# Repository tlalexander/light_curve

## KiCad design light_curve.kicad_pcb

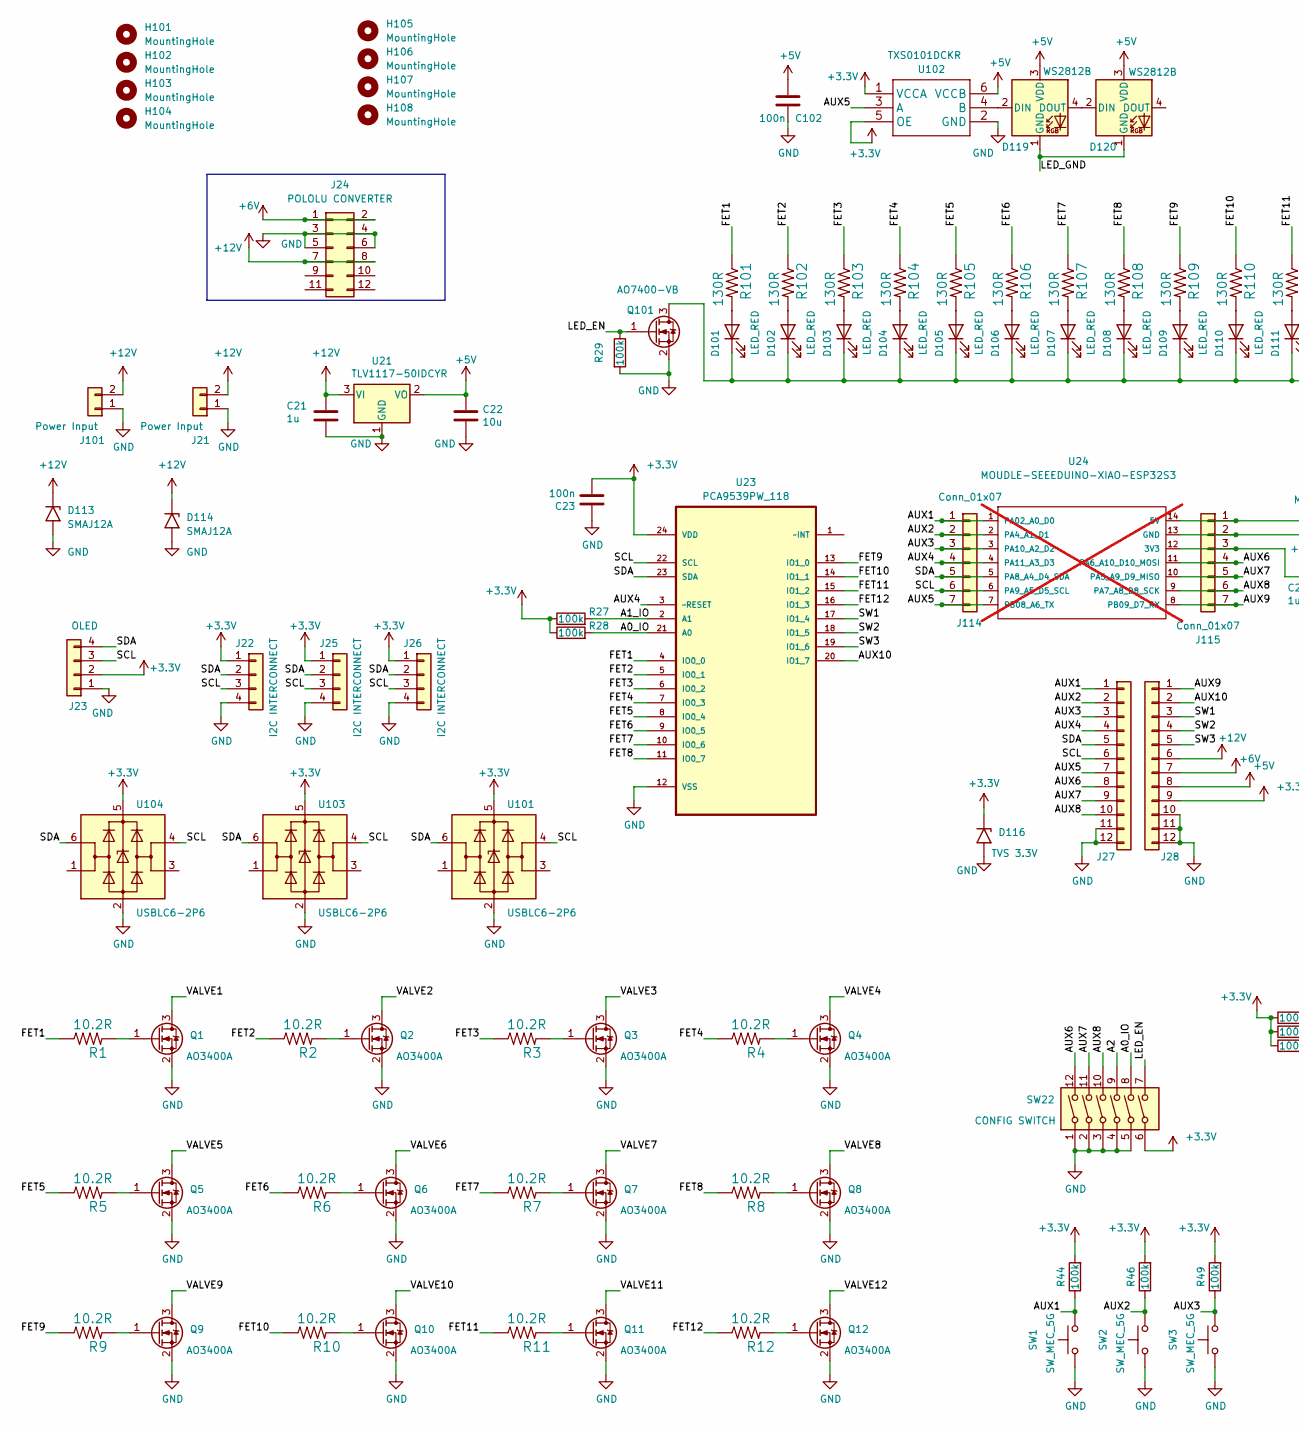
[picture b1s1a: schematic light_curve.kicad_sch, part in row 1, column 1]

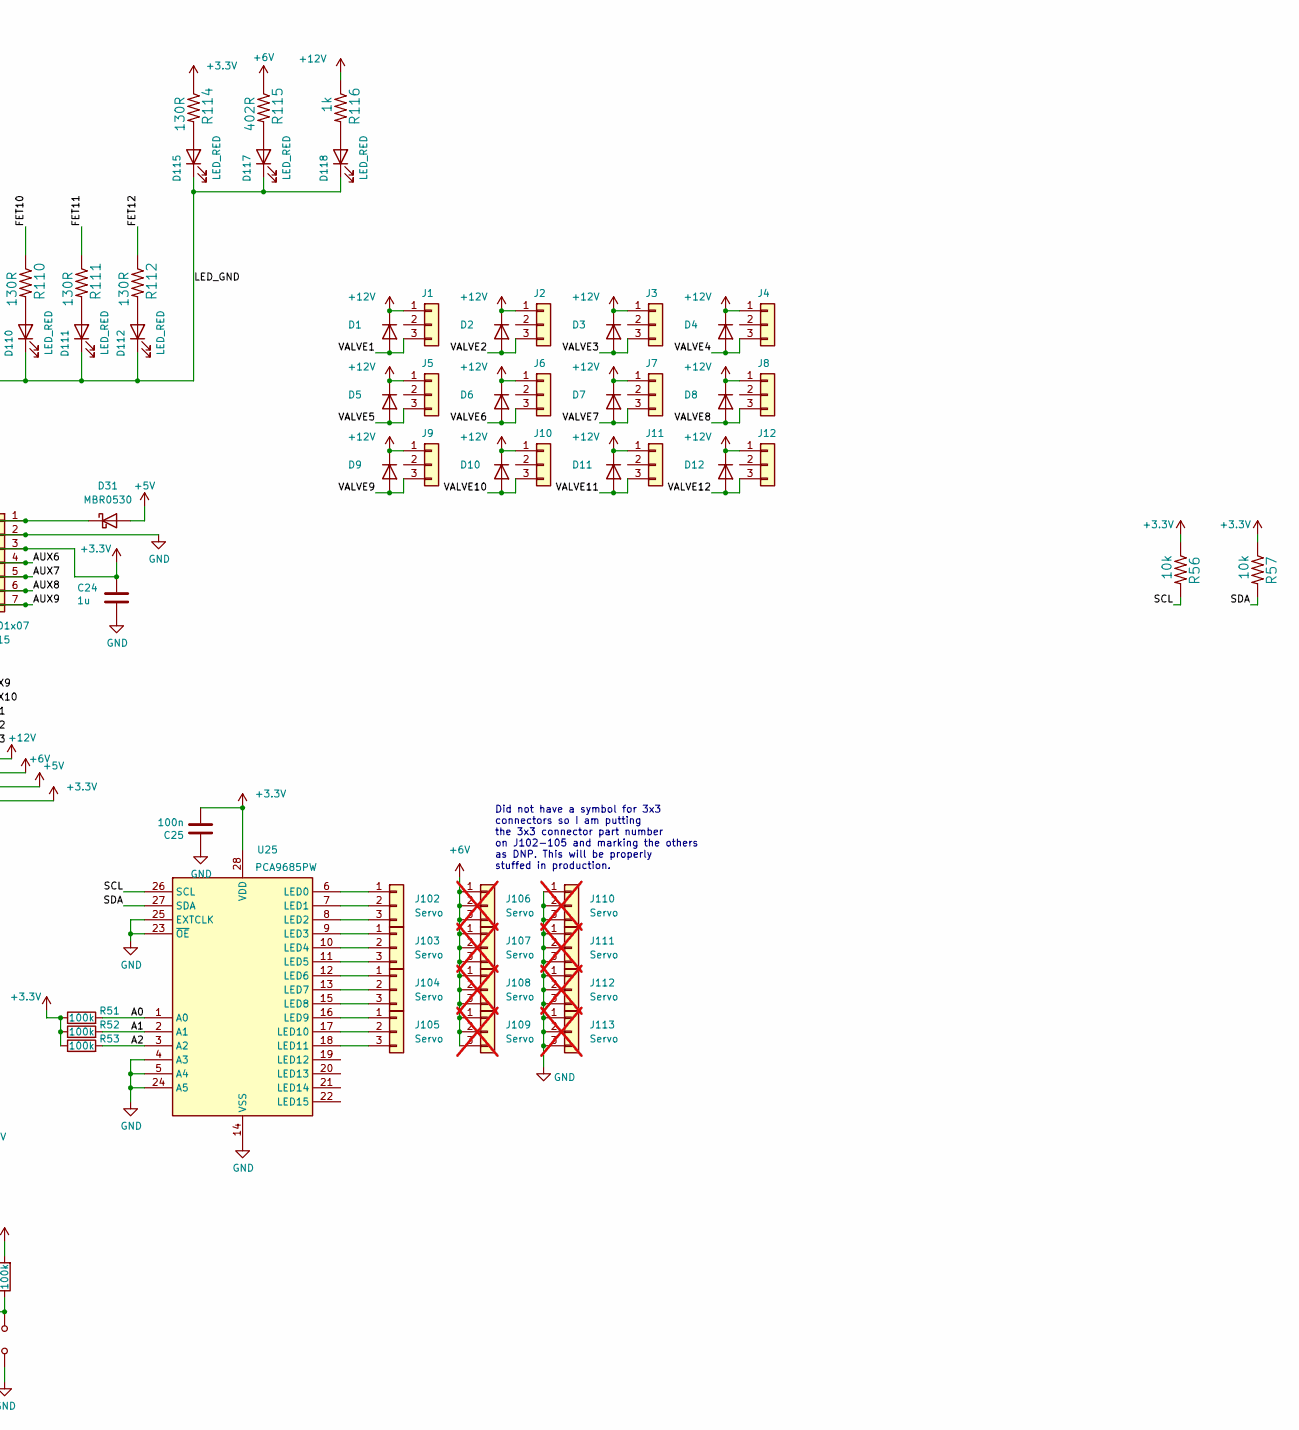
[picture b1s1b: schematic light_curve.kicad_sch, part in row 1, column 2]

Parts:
C21, C24: 1u; C_0603_1608Metric; LCSC C15849
C22: 10u; C_0805_2012Metric; LCSC C15850
C23, C25, C102: 100n; C_0603_1608Metric; LCSC C14663
D1, D2, D3, D4, D5, D6, D7, D8, D9, D10, D11, D12: D; D_SMA; LCSC C95872
D31: MBR0530; D_SOD-123; LCSC C77336
D101, D102, D103, D104, D105, D106, D107, D108, D109, D110, D111, D112, D115, D117, D118: LED_RED; LED_0603_1608Metric; MPN LTST-C150KRKT; Digikey 160-1405-1-ND
D113, D114: SMAJ12A; D_SMA; LCSC C89613
D116: TVS 3.3V; D_SOD-523; MPN ESD5Z3V3; LCSC C2841409
D119, D120: WS2812B; LED_WS2812_3528_3.5x2.8mm_P1.5mm; LCSC C2890364
H101, H102, H103, H104: MountingHole; MountingHole_4.5mm
H105, H106, H107, H108: MountingHole; MountingHole_2.5mm
J1, J2, J3, J4, J5, J6, J7, J8, J9, J10, J11, J12: Valve Conn; BOOMELE-2510-3A_1x03_P2.54mm_Vertical; LCSC C509148
J21, J101: Power Input; AMASS_XT30PW-F_1x02_P2.50mm_Horizontal; LCSC C2913282
J22, J25, J26: I2C INTERCONNECT; PINREX-744-81-04TW00 _1x04_P2.54mm_Vertical; LCSC C2982033
J23: OLED; PinHeader_1x04_P2.54mm_Vertical; LCSC C2718488
J24: POLOLU CONVERTER; PinHeader_2x06_P2.54mm_Vertical
J27, J28: A2541WV-12P; PinHeader_1x12_P2.54mm_Vertical; LCSC C1121851
J102, J103, J104, J105: Servo; PinHeader_1x03_P2.54mm_Vertical; LCSC C7429377
J106, J107, J108, J109, J110, J111, J112, J113: Servo; PinHeader_1x03_P2.54mm_Vertical; not fitted
J114, J115: Conn_01x07; PinSocket_1x07_P2.54mm_Vertical; LCSC C2897370
Q1, Q2, Q3, Q4, Q5, Q6, Q7, Q8, Q9, Q10, Q11, Q12: AO3400A; SOT-23; LCSC C347475
Q101: AO7400-VB; SOT-323_SC-70; LCSC C879165
R1, R2, R3, R4, R5, R6, R7, R8, R9, R10, R11, R12: 10.2R; R_0603_1608Metric; LCSC C2933129
R27, R28, R29, R44, R46, R49, R51, R52, R53: 100k; R_0603_1608Metric; LCSC C14675
R56, R57: 10k; R_0603_1608Metric; LCSC C25804
R101, R102, R103, R104, R105, R106, R107, R108, R109, R110, R111, R112, R114: 130R; R_0603_1608Metric; LCSC C22796
R115: 402R; R_0603_1608Metric; LCSC C2683044
R116: 1k; R_0603_1608Metric; LCSC C253329
SW1, SW2, SW3: SW_MEC_5G; SW_TS_1101_C_W; LCSC C318938
SW22: CONFIG SWITCH; SW_DIP_SPSTx06_Slide_KingTek_DSHP06TS_W7.62mm_P1.27mm; LCSC C40737
U21: TLV1117-50IDCYR; SOT-223-3_TabPin2; LCSC C15512
U23: PCA9539PW_118; TSSOP-24_4.4x7.8mm_P0.65mm; MPN PCA9539PW,118; LCSC C2687996
U24: MOUDLE-SEEEDUINO-XIAO-ESP32S3; MOUDLE14P-SMD-2.54-21X17.8MM; not fitted
U25: PCA9685PW; TSSOP-28_4.4x9.7mm_P0.65mm; LCSC C2678753
U101, U103, U104: USBLC6-2P6; SOT-666; LCSC C2827693
U102: TXS0101DCKR; SOT-363_SC-70-6; LCSC C132031

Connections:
+3.3V: C23.2, C24.1, C25.2, D116.1 (A1), J22.1, J23.2, J25.1, J26.1, J28.9, J115.3, R27.1, R28.1, R44.2, R46.2, R49.2, R51.1, R52.1, R53.1, R56.1, R57.1, R114.1, SW22.6, U23.24 (VDD), U24.12 (3V3), U25.28 (VDD), U101.5 (VBUS), U102.1 (VCCA), U102.5 (OE), U103.5 (VBUS), U104.5 (VBUS)
+5V: C22.1, C102.1, D31.2 (A), D119.3 (VDD), D120.3 (VDD), J28.8, U21.2 (VO), U102.6 (VCCB)
+6V: J24.1, J24.2, J28.7, J106.1, J106.2, J106.3, J107.1, J107.2, J107.3, J108.1, J108.2, J108.3, J109.1, J109.2, J109.3, R115.1
+12V: C21.1, D1.1 (K), D2.1 (K), D3.1 (K), D4.1 (K), D5.1 (K), D6.1 (K), D7.1 (K), D8.1 (K), D9.1 (K), D10.1 (K), D11.1 (K), D12.1 (K), D113.1 (A1), D114.1 (A1), J1.1, J2.1, J3.1, J4.1, J5.1, J6.1, J7.1, J8.1, J9.1, J10.1, J11.1, J12.1, J21.2, J24.7, J24.8, J28.6, J101.2, R116.1, U21.3 (VI)
/A0: R51.2, U25.1 (A0)
/A0_IO: R28.2, SW22.8, U23.21 (A0)
/A1: R52.2, U25.2 (A1)
/A1_IO: R27.2, U23.2 (A1)
/A2: R53.2, SW22.9, U25.3 (A2)
/AUX1: J27.1, J114.1, R44.1, SW1.2, U24.1 (PA02_A0_D0)
/AUX2: J27.2, J114.2, R46.1, SW2.2, U24.2 (PA4_A1_D1)
/AUX3: J27.3, J114.3, R49.1, SW3.2, U24.3 (PA10_A2_D2)
/AUX4: J27.4, J114.4, U23.3 (~RESET), U24.4 (PA11_A3_D3)
/AUX5: J27.7, J114.7, U24.7 (PB08_A6_TX), U102.3 (A)
/AUX6: J27.8, J115.4, SW22.12, U24.11 (PA6_A10_D10_MOSI)
/AUX7: J27.9, J115.5, SW22.11, U24.10 (PA5_A9_D9_MISO)
/AUX8: J27.10, J115.6, SW22.10, U24.9 (PA7_A8_D8_SCK)
/AUX9: J28.1, J115.7, U24.8 (PB09_D7_RX)
/AUX10: J28.2, U23.20 (IO1_7)
/FET1: R1.1, R101.1, U23.4 (IO0_0)
/FET2: R2.1, R102.1, U23.5 (IO0_1)
/FET3: R3.1, R103.1, U23.6 (IO0_2)
/FET4: R4.1, R104.1, U23.7 (IO0_3)
/FET5: R5.1, R105.1, U23.8 (IO0_4)
/FET6: R6.1, R106.1, U23.9 (IO0_5)
/FET7: R7.1, R107.1, U23.10 (IO0_6)
/FET8: R8.1, R108.1, U23.11 (IO0_7)
/FET9: R9.1, R109.1, U23.13 (IO1_0)
/FET10: R10.1, R110.1, U23.14 (IO1_1)
/FET11: R11.1, R111.1, U23.15 (IO1_2)
/FET12: R12.1, R112.1, U23.16 (IO1_3)
/LED_EN: Q101.1 (G), R29.1, SW22.7
/LED_GND: D101.1 (K), D102.1 (K), D103.1 (K), D104.1 (K), D105.1 (K), D106.1 (K), D107.1 (K), D108.1 (K), D109.1 (K), D110.1 (K), D111.1 (K), D112.1 (K), D115.1 (K), D117.1 (K), D118.1 (K), D119.1 (GND), D120.1 (GND), Q101.3 (D)
/SCL: J22.3, J23.3, J25.3, J26.3, J27.6, J114.6, R56.2, U23.22 (SCL), U24.6 (PA9_A5_D5_SCL), U25.26 (SCL), U101.4 (I/O2), U103.4 (I/O2), U104.4 (I/O2)
/SDA: J22.2, J23.4, J25.2, J26.2, J27.5, J114.5, R57.2, U23.23 (SDA), U24.5 (PA8_A4_D4_SDA), U25.27 (SDA), U101.6 (I/O1), U103.6 (I/O1), U104.6 (I/O1)
/SW1: J28.3, U23.17 (IO1_4)
/SW2: J28.4, U23.18 (IO1_5)
/SW3: J28.5, U23.19 (IO1_6)
/VALVE1: D1.2 (A), J1.3, Q1.3 (D)
/VALVE2: D2.2 (A), J2.3, Q2.3 (D)
/VALVE3: D3.2 (A), J3.3, Q3.3 (D)
/VALVE4: D4.2 (A), J4.3, Q4.3 (D)
/VALVE5: D5.2 (A), J5.3, Q5.3 (D)
/VALVE6: D6.2 (A), J6.3, Q6.3 (D)
/VALVE7: D7.2 (A), J7.3, Q7.3 (D)
/VALVE8: D8.2 (A), J8.3, Q8.3 (D)
/VALVE9: D9.2 (A), J9.3, Q9.3 (D)
/VALVE10: D10.2 (A), J10.3, Q10.3 (D)
/VALVE11: D11.2 (A), J11.3, Q11.3 (D)
/VALVE12: D12.2 (A), J12.3, Q12.3 (D)
GND: C21.2, C22.2, C23.1, C24.2, C25.1, C102.2, D113.2 (A2), D114.2 (A2), D116.2 (A2), J21.1, J22.4, J23.1, J24.3, J24.4, J24.5, J24.6, J25.4, J26.4, J27.11, J27.12, J28.10, J28.11, J28.12, J101.1, J110.1, J110.2, J110.3, J111.1, J111.2, J111.3, J112.1, J112.2, J112.3, J113.1, J113.2, J113.3, J115.2, Q1.2 (S), Q2.2 (S), Q3.2 (S), Q4.2 (S), Q5.2 (S), Q6.2 (S), Q7.2 (S), Q8.2 (S), Q9.2 (S), Q10.2 (S), Q11.2 (S), Q12.2 (S), Q101.2 (S), R29.2, SW1.1, SW2.1, SW3.1, SW22.1, SW22.2, SW22.3, SW22.4, SW22.5, U21.1 (GND), U23.12 (VSS), U24.13 (GND), U25.4 (A3), U25.5 (A4), U25.14 (VSS), U25.23 (~OE), U25.24 (A5), U25.25 (EXTCLK), U101.2 (GND), U102.2 (GND), U103.2 (GND), U104.2 (GND)
unnamed: D31.1 (K), J115.1, U24.14 (5V)
unnamed: D101.2 (A), R101.2
unnamed: D102.2 (A), R102.2
unnamed: D103.2 (A), R103.2
unnamed: D104.2 (A), R104.2
unnamed: D105.2 (A), R105.2
unnamed: D106.2 (A), R106.2
unnamed: D107.2 (A), R107.2
unnamed: D108.2 (A), R108.2
unnamed: D109.2 (A), R109.2
unnamed: D110.2 (A), R110.2
unnamed: D111.2 (A), R111.2
unnamed: D112.2 (A), R112.2
unnamed: D115.2 (A), R114.2
unnamed: D117.2 (A), R115.2
unnamed: D118.2 (A), R116.2
unnamed: D119.2 (DIN), U102.4 (B)
unnamed: D119.4 (DOUT), D120.2 (DIN)
unnamed: J102.1, U25.6 (LED0)
unnamed: J102.2, U25.7 (LED1)
unnamed: J102.3, U25.8 (LED2)
unnamed: J103.1, U25.9 (LED3)
unnamed: J103.2, U25.10 (LED4)
unnamed: J103.3, U25.11 (LED5)
unnamed: J104.1, U25.12 (LED6)
unnamed: J104.2, U25.13 (LED7)
unnamed: J104.3, U25.15 (LED8)
unnamed: J105.1, U25.16 (LED9)
unnamed: J105.2, U25.17 (LED10)
unnamed: J105.3, U25.18 (LED11)
unnamed: Q1.1 (G), R1.2
unnamed: Q2.1 (G), R2.2
unnamed: Q3.1 (G), R3.2
unnamed: Q4.1 (G), R4.2
unnamed: Q5.1 (G), R5.2
unnamed: Q6.1 (G), R6.2
unnamed: Q7.1 (G), R7.2
unnamed: Q8.1 (G), R8.2
unnamed: Q9.1 (G), R9.2
unnamed: Q10.1 (G), R10.2
unnamed: Q11.1 (G), R11.2
unnamed: Q12.1 (G), R12.2

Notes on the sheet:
Did not have a symbol for 3x3 connectors so I am putting the 3x3 connector part number on J102-105 and marking the others as DNP. This will be properly stuffed in production.

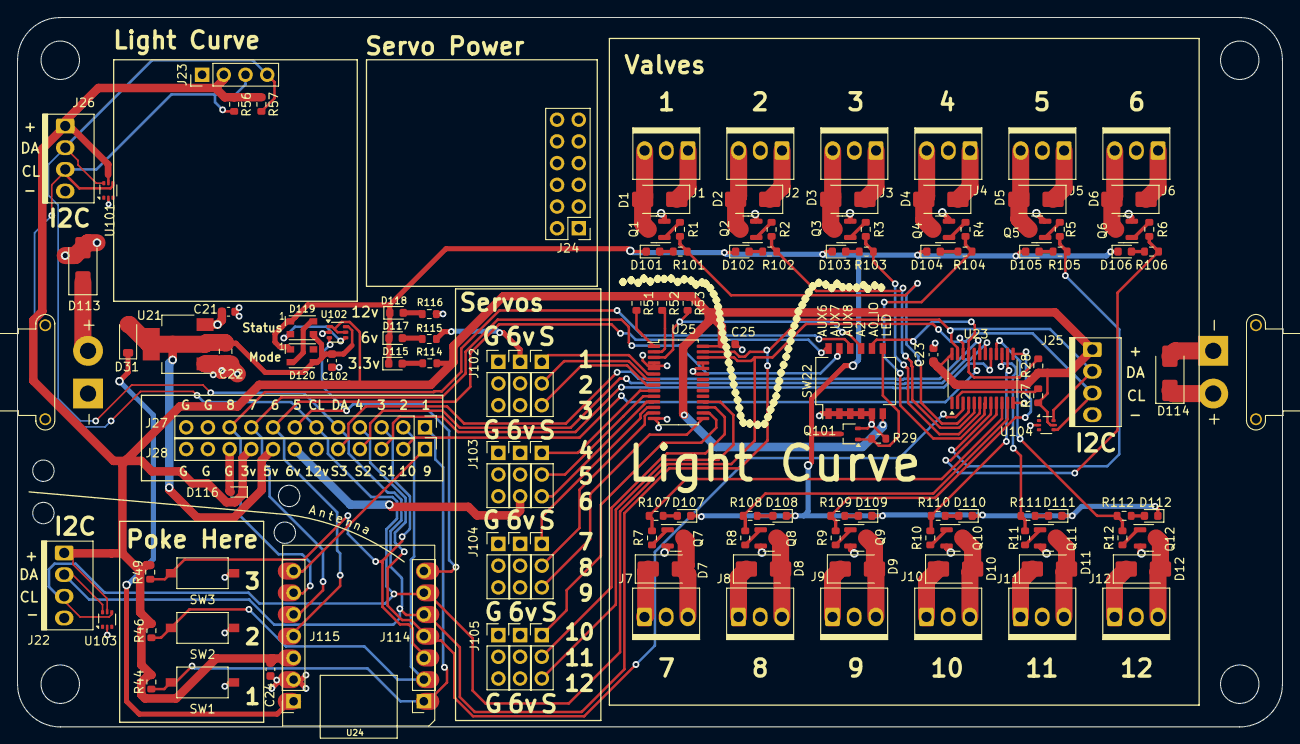
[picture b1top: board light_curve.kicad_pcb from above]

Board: 4 copper layers, 148.0 x 83.0 mm, 145 parts (0 on the bottom side), 93 nets.

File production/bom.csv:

Designator,Footprint,Quantity,Value,LCSC Part #
"C102, C23, C25",0603,3,100n,C14663
"C21, C24",0603,2,1u,C15849
C22,0805,1,10u,C15850
"D1, D10, D11, D12, D2, D3, D4, D5, D6, D7, D8, D9",D_SMA,12,D,C95872
"D101, D102, D103, D104, D105, D106, D107, D108, D109, D110, D111, D112, D115, D117, D118",0603,15,LED_RED,C434419
"D113, D114",D_SMA,2,SMAJ12A,C89613
D116,D_SOD-523,1,TVS 3.3V,C2841409
"D119, D120",LED_WS2812_3528_3.5x2.8mm_P1.5mm,2,WS2812B,C2890364
D31,D_SOD-123,1,MBR0530,C77336
"H101, H102, H103, H104",MountingHole_4.5mm,4,MountingHole,
"H105, H106, H107, H108",MountingHole_2.5mm,4,MountingHole,
"J1, J10, J11, J12, J2, J3, J4, J5, J6, J7, J8, J9",BOOMELE-2510-3A_1x03_P2.54mm_Vertical,12,Valve Conn,C509148
"J101, J21",AMASS_XT30PW-F_1x02_P2.50mm_Horizontal,2,Power Input,C2913282
"J102, J103, J104, J105",PinHeader_1x03_P2.54mm_Vertical,4,Servo,C7429377
"J114, J115",PinSocket_1x07_P2.54mm_Vertical,2,Conn_01x07,C2897370
"J22, J25, J26",PINREX-744-81-04TW00 _1x04_P2.54mm_Vertical,3,I2C INTERCONNECT,C2982033
J23,PinHeader_1x04_P2.54mm_Vertical,1,OLED,C2718488
J24,PinHeader_2x06_P2.54mm_Vertical,1,POLOLU CONVERTER,
"J27, J28",PinHeader_1x12_P2.54mm_Vertical,2,A2541WV-12P,C1121851
"Q1, Q10, Q11, Q12, Q2, Q3, Q4, Q5, Q6, Q7, Q8, Q9",SOT-23,12,AO3400A,C347475
Q101,SOT-323_SC-70,1,AO7400-VB,C879165
"R1, R10, R11, R12, R2, R3, R4, R5, R6, R7, R8, R9",0603,12,10.2R,C2933129
"R101, R102, R103, R104, R105, R106, R107, R108, R109, R110, R111, R112, R114",0603,13,130R,C22796
R115,0603,1,402R,C2683044
R116,0603,1,1k,C253329
"R27, R28, R29, R44, R46, R49, R51, R52, R53",0603,9,100k,C14675
"R56, R57",0603,2,10k,C25804
"SW1, SW2, SW3",SW_TS_1101_C_W,3,SW_MEC_5G,C318938
SW22,SW_DIP_SPSTx06_Slide_KingTek_DSHP06TS_W7.62mm_P1.27mm,1,CONFIG SWITCH,C40737
"U101, U103, U104",SOT-666,3,USBLC6-2P6,C2827693
U102,SOT-363_SC-70-6,1,TXS0101DCKR,C132031
U21,SOT-223-3_TabPin2,1,TLV1117-50IDCYR,C15512
U23,TSSOP-24_4.4x7.8mm_P0.65mm,1,PCA9539PW_118,C2687996
U25,TSSOP-28_4.4x9.7mm_P0.65mm,1,PCA9685PW,C2678753

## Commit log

2024-05-08 Initial commit.
2024-08-14 Update boards for last minute order before the burn! As ordered.
